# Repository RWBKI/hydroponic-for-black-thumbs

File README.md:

# Hydroponic for Black Thumbs

> I couldn't even grow parsley. So I asked Claude for help… and things got a little out of hand.

A home-built, 24-site hydroponic tower, the growing method that keeps it alive, a dashboard that tells you what to do today, a Claude plugin that sets that dashboard up for your own tower, and the (still untested) electronics and firmware meant to automate it. Everything here was worked out in conversation with Claude by someone who started with zero hydroponics knowledge.

This is an independent community project. It is not affiliated with or endorsed by Anthropic.

<p align="center"><em>The dashboard: type your readings, it tells you what to do today. Runs on demo data until you press "Start fresh".</em><br><strong><a href="https://rwbki.github.io/hydroponic-for-black-thumbs/dashboard/">▶ Try it live in your browser</a></strong><br><em><a href="dashboard/">Download it</a> or let the <a href="plugins/hydroponic-for-black-thumbs/">Claude plugin</a> set it up for your tower.</em></p>

<h3 align="center">The results</h3>

<p align="center"><em>Two neighbouring parsley plants, one stem cut from each. Soil on the left, tower on the right.</em></p>

## What works and what doesn't (yet)

Read this table before you copy anything.

| Part | Status |
|---|---|
| The tower: 24 sites, one shared reservoir, leafy greens and herbs | Running since September 2026 |
| [Growing guide](docs/growing-guide.md): doses, mixing order, routine, troubleshooting | In daily use on the real tower |
| [Dashboard](dashboard/): enter pH / EC / level, get today's actions | Rewritten in English from the one in daily use on the real tower |
| [Claude plugin](plugins/hydroponic-for-black-thumbs/): sets up the dashboard for your tower and coaches you | Works in the Claude app |
| [Automation plan](docs/automation-plan.md): sensors, dosing rules, safeguards | Designed, not built |
| [Wiring guide](docs/wiring.md): module-based controller, pin by pin | Designed, parts ordered, not assembled |
| [Custom PCB v1.1](docs/pcb.md) | Designed, [reviewed](hardware/pcb/docs/REVIEW-rev1.0.md), revised and [reviewed again](hardware/pcb/docs/REVIEW-rev1.1.md): **never fabricated, untested** |
| [Firmware](firmware/) for the ESP32: readings, web page, dosing with safeguards | Written, compiles, dosing logic covered by automated tests. **Never run on hardware** |

Building the tower itself is not covered: there are plenty of tutorials for that. This repository covers what comes after.

If you are an electronics engineer, the most useful thing you can do is review the schematic. See [CONTRIBUTING.md](CONTRIBUTING.md).

## The tower in numbers

| | |
|---|---|
| Sites | 24, in 4 columns of 6 |
| Reservoir | 37 L (started at 15 L, which drifted too fast) |
| Medium | Expanded clay pebbles, with a coco or rockwool plug at the collar |
| Nutrients | Terra Aquatica TriPart (Micro, Grow, Bloom) |
| Targets | EC 1.0 to 1.2 mS/cm, pH 6.0 (5.5 to 6.5 acceptable) |
| Light | Natural light only, under an open-sided shelter |
| Crops | Lettuce, basil, chives, parsley, lamb's lettuce, spinach |
| Routine | 3 minutes every 2 to 3 days; full drain every 15 to 21 days |

## Where to start

**I want to grow things.** Read the [growing guide](docs/growing-guide.md). You need a pH meter, an EC meter and pH Down. Nothing in it requires electronics.

**I want to try the dashboard.** Download [`dashboard/index.html`](dashboard/index.html) and open it in a browser. It starts with demo data, needs no server or account, and keeps your data in that browser.

**I want it in my own Claude.** Install the plugin (below). Claude asks a few questions about your tower, water and nutrients, creates your dashboard, and then advises you from your own readings.

**I want to automate.** Read the [automation plan](docs/automation-plan.md) first, safeguards included, then the [wiring guide](docs/wiring.md) and the [firmware](firmware/). The [PCB](docs/pcb.md) is optional and unproven.

**I want to know what it costs.** See [costs](docs/costs.md). Short version: the automation parts come to roughly €200.

## Use it with Claude

The plugin contains one skill, `hydroponic-tower-coach`.

**Claude apps, as a plugin** (paid plans): Customize → Plugins → Personal plugins → "+" → Add marketplace → Add from a repository, then paste this repository's URL and install `hydroponic-for-black-thumbs`.

**Claude apps, as a skill only** (all plans): download `hydroponic-tower-coach.zip` from the Releases page, then Customize → Skills → "+" → Create skill → Upload a skill.

**Claude Code:**

```
/plugin marketplace add RWBKI/hydroponic-for-black-thumbs
/plugin install hydroponic-for-black-thumbs@hydroponic-for-black-thumbs
```

Then say: "Set up my hydroponic tower dashboard."

Later, press "Copy summary for Claude" on the dashboard, paste it into a conversation and ask your question.

Menu names may change; see Anthropic's help pages on [skills](https://support.claude.com/en/articles/12512180-use-skills-in-claude) and [plugins](https://support.claude.com/en/articles/13851150-install-financial-services-plugins).

## Safety

- Water and electricity share a box in this project. No mains voltage goes inside the controller enclosure: the 12 V power brick stays dry, on an outdoor socket protected by an RCD/GFCI.
- pH Down is acid. Add it in small doses to the full volume of water, never to other concentrates.
- Automated dosing can kill a reservoir faster than neglect. The [safeguards](docs/automation-plan.md#safeguards-before-autonomy) are not optional.
- The doses in this repo were calibrated on one water supply and one EC pen. Measure yours.

## Licence

- Code (dashboard, firmware, plugin): [MIT](LICENSE)
- Hardware (schematic, PCB): [CERN-OHL-P v2](hardware/LICENSE)
- Documentation and photos: [CC BY 4.0](docs/LICENSE)

Copyright © 2026 RWBKI and contributors. To credit the project: "Hydroponic for Black Thumbs, by RWBKI and contributors", with a link to this repository.

## Origin

The project was first shared on r/ClaudeAI in November 2026. The questions asked there shaped this repository.

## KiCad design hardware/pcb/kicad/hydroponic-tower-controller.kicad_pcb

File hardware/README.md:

# Hardware

| Folder | Contents |
|---|---|
| `pcb/kicad/` | KiCad 7 project: schematic, routed board, two project footprints |
| `pcb/fabrication/` | Gerbers and drill files (zip), BOM and placement file for JLCPCB assembly |
| `pcb/docs/` | Schematic and assembly drawing as PDF, the two design reviews |
| `pcb/images/` | Layout and silkscreen views |
| `pcb/tools/` | Scripts that re-check the isolation gap, the guard ring and schematic against board |
| `pcb/CHANGES.md` | What changed in rev 1.1 |

**The board has never been fabricated.** Read [docs/pcb.md](../docs/pcb.md) before using anything here.

Hardware in this folder is released under [CERN-OHL-P v2](LICENSE).

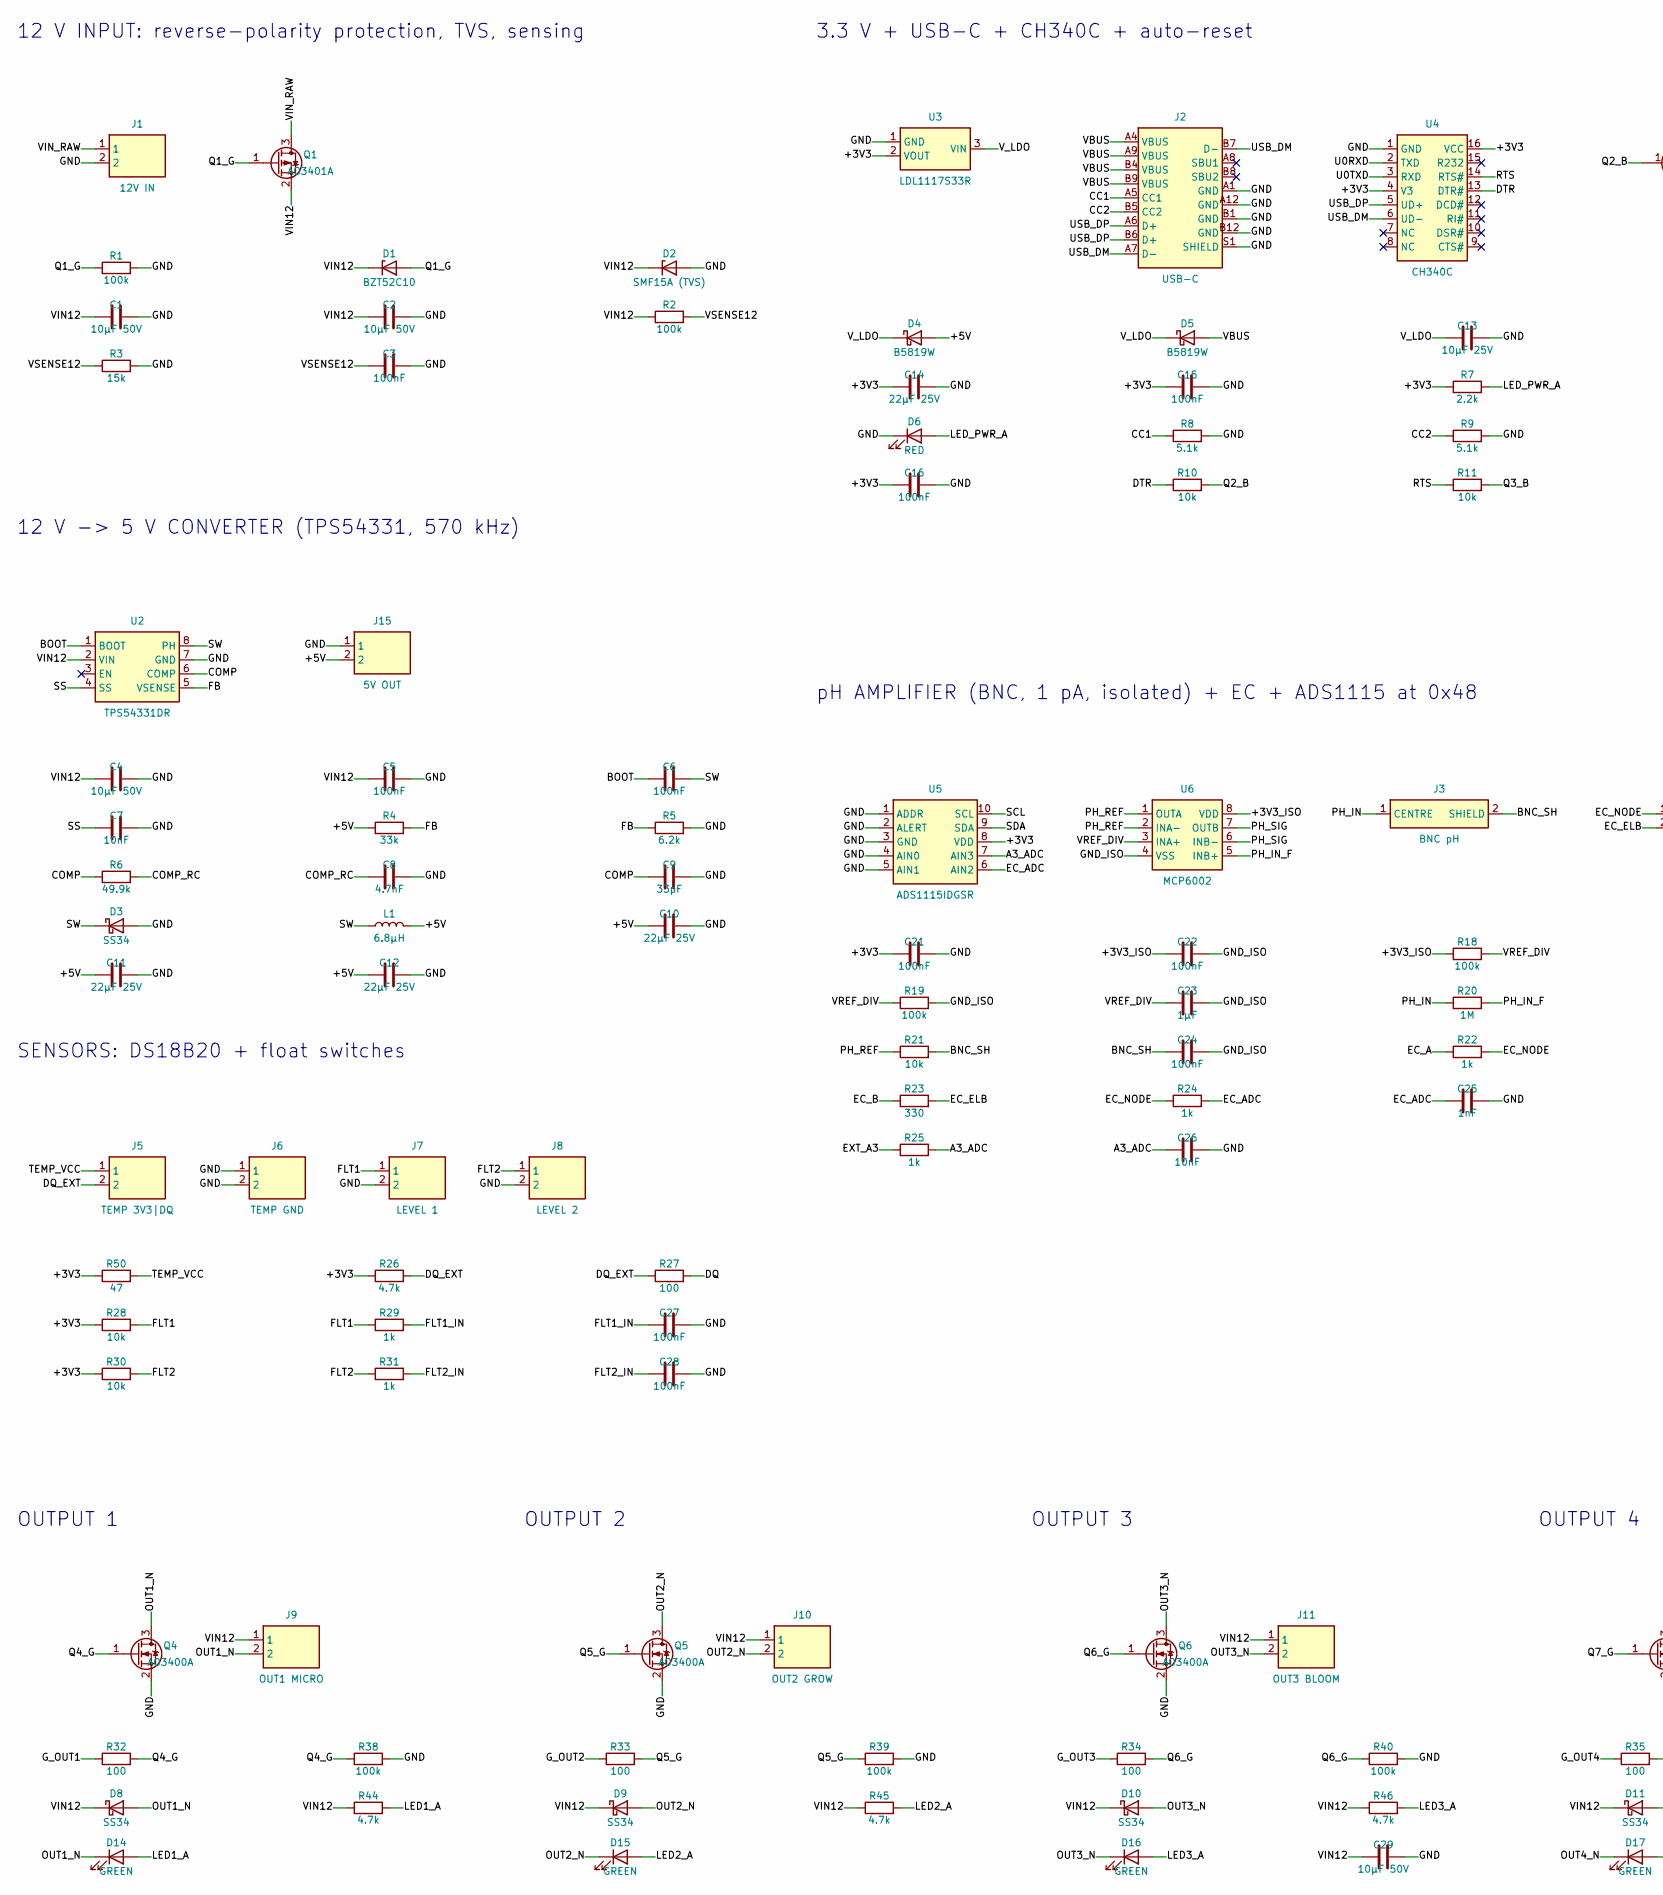
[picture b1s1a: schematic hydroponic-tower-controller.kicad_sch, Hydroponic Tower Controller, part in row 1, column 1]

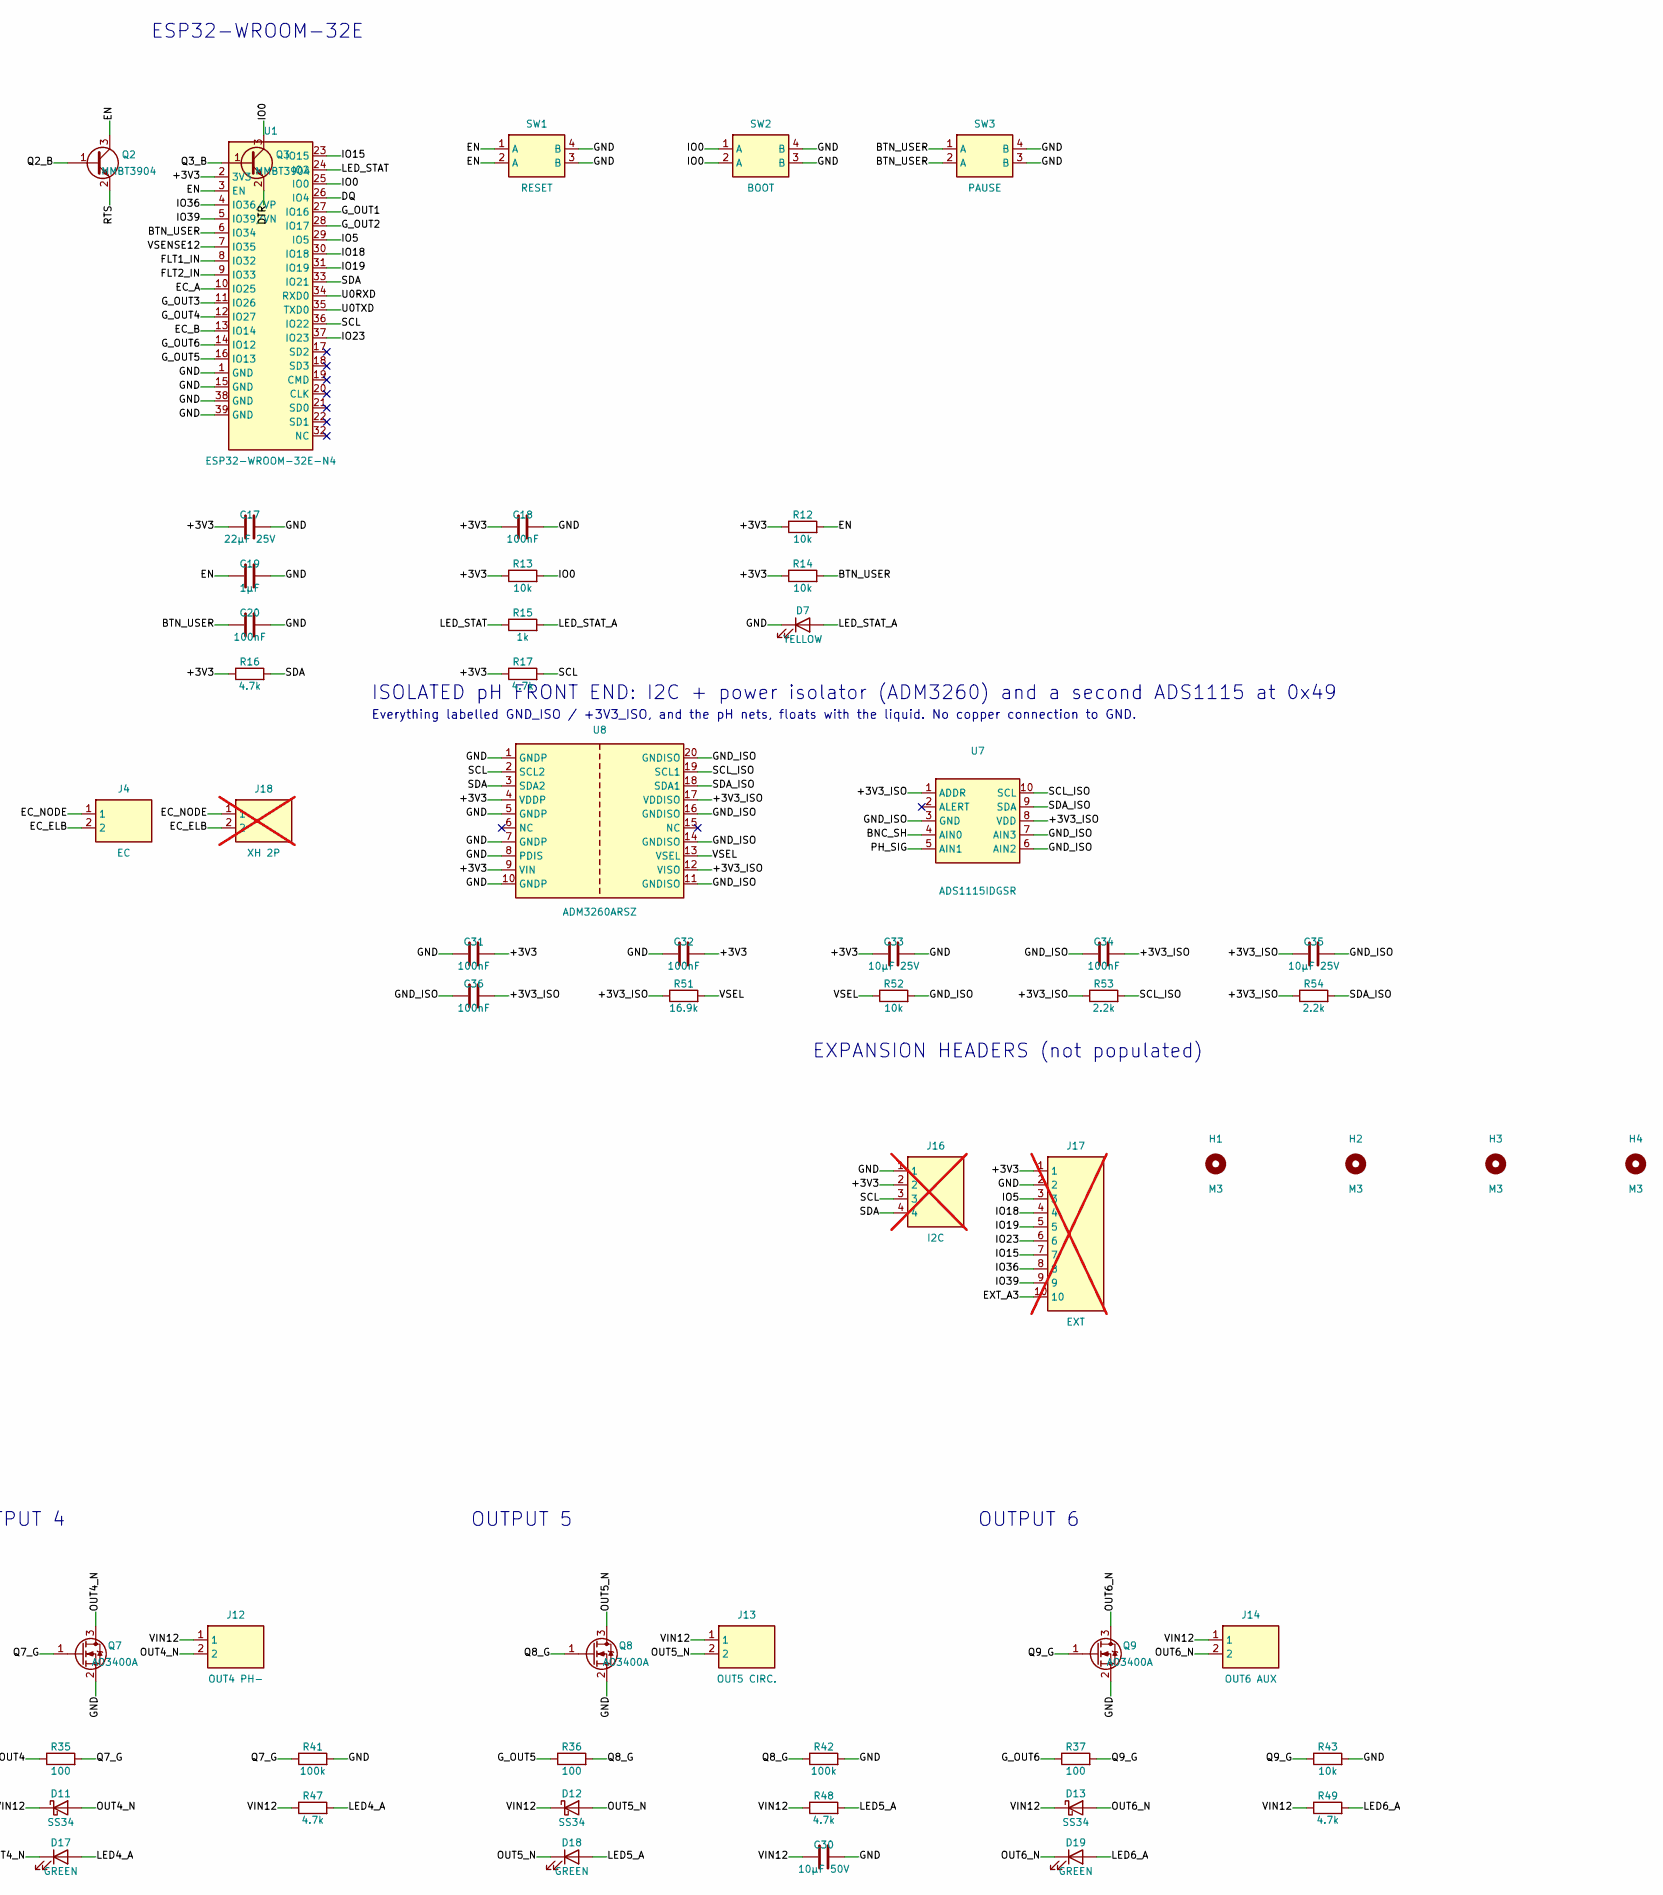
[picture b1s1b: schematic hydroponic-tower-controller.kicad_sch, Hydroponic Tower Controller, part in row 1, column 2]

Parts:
C1, C2, C4, C29, C30: 10µF 50V; C_1206_3216Metric; LCSC C13585
C3, C5, C6, C15, C16, C18, C20, C21, C22, C24, C27, C28, C31, C32, C36: 100nF; C_0603_1608Metric; LCSC C14663
C7, C26: 10nF; C_0603_1608Metric; LCSC C57112
C8: 4.7nF; C_0603_1608Metric; LCSC C53987
C9: 33pF; C_0603_1608Metric; LCSC C1663
C10, C11, C12: 22µF 25V; C_1206_3216Metric; LCSC C12891
C13, C33, C35: 10µF 25V; C_0805_2012Metric; LCSC C15850
C14, C17: 22µF 25V; C_0805_2012Metric; LCSC C45783
C19, C23: 1µF; C_0603_1608Metric; LCSC C15849
C25: 1nF; C_0603_1608Metric; LCSC C1588
C34: 100nF; C_0402_1005Metric; LCSC C1525
D1: BZT52C10; D_SOD-123; LCSC C19077408
D2: SMF15A (TVS); D_SOD-123F; LCSC C19077509
D3, D8, D9, D10, D11, D12, D13: SS34; D_SMA; LCSC C8678
D4, D5: B5819W; D_SOD-123; LCSC C8598
D6: RED; LED_0603_1608Metric; LCSC C2286
D7: YELLOW; LED_0805_2012Metric; LCSC C2296
D14, D15, D16, D17, D18, D19: GREEN; LED_0805_2012Metric; LCSC C2297
H1, H2, H3, H4: M3; MountingHole_3.2mm_M3
J1: 12V IN; TerminalBlock_Phoenix_MKDS-1,5-2_1x02_P5.00mm_Horizontal; LCSC C474881
J2: USB-C; USB_C_Receptacle_HRO_TYPE-C-31-M-12; LCSC C165948
J3: BNC pH; BNC_Amphenol_B6252HB-NPP3G-50_Horizontal; LCSC C22457552
J4: EC; TerminalBlock_Phoenix_MKDS-1,5-2_1x02_P5.00mm_Horizontal; LCSC C474881
J5: TEMP 3V3|DQ; TerminalBlock_Phoenix_MKDS-1,5-2_1x02_P5.00mm_Horizontal; LCSC C474881
J6: TEMP GND; TerminalBlock_Phoenix_MKDS-1,5-2_1x02_P5.00mm_Horizontal; LCSC C474881
J7: LEVEL 1; TerminalBlock_Phoenix_MKDS-1,5-2_1x02_P5.00mm_Horizontal; LCSC C474881
J8: LEVEL 2; TerminalBlock_Phoenix_MKDS-1,5-2_1x02_P5.00mm_Horizontal; LCSC C474881
J9: OUT1 MICRO; TerminalBlock_Phoenix_MKDS-1,5-2_1x02_P5.00mm_Horizontal; LCSC C474881
J10: OUT2 GROW; TerminalBlock_Phoenix_MKDS-1,5-2_1x02_P5.00mm_Horizontal; LCSC C474881
J11: OUT3 BLOOM; TerminalBlock_Phoenix_MKDS-1,5-2_1x02_P5.00mm_Horizontal; LCSC C474881
J12: OUT4 PH-; TerminalBlock_Phoenix_MKDS-1,5-2_1x02_P5.00mm_Horizontal; LCSC C474881
J13: OUT5 CIRC.; TerminalBlock_Phoenix_MKDS-1,5-2_1x02_P5.00mm_Horizontal; LCSC C474881
J14: OUT6 AUX; TerminalBlock_Phoenix_MKDS-1,5-2_1x02_P5.00mm_Horizontal; LCSC C474881
J15: 5V OUT; TerminalBlock_Phoenix_MKDS-1,5-2_1x02_P5.00mm_Horizontal; LCSC C474881
J16: I2C; PinHeader_1x04_P2.54mm_Vertical; not fitted
J17: EXT; PinHeader_1x10_P2.54mm_Vertical; not fitted
J18: XH 2P; JST_XH_B2B-XH-A_1x02_P2.50mm_Vertical; not fitted
L1: 6.8µH; L_Cenker_CKCS6045; LCSC C354631
Q1: AO3401A; SOT-23; LCSC C15127
Q2, Q3: MMBT3904; SOT-23; LCSC C20526
Q4, Q5, Q6, Q7, Q8, Q9: AO3400A; SOT-23; LCSC C20917
R1, R2, R18, R19, R38, R39, R40, R41, R42: 100k; R_0603_1608Metric; LCSC C25803
R3: 15k; R_0603_1608Metric; LCSC C22809
R4: 33k; R_0603_1608Metric; LCSC C4216
R5: 6.2k; R_0603_1608Metric; LCSC C4260
R6: 49.9k; R_0603_1608Metric; LCSC C23184
R7, R53, R54: 2.2k; R_0603_1608Metric; LCSC C4190
R8, R9: 5.1k; R_0603_1608Metric; LCSC C23186
R10, R11, R12, R13, R14, R21, R28, R30, R43, R52: 10k; R_0603_1608Metric; LCSC C25804
R15, R22, R24, R25, R29, R31: 1k; R_0603_1608Metric; LCSC C21190
R16, R17, R26, R44, R45, R46, R47, R48, R49: 4.7k; R_0603_1608Metric; LCSC C23162
R20: 1M; R_0603_1608Metric; LCSC C22935
R23: 330; R_0603_1608Metric; LCSC C23138
R27, R32, R33, R34, R35, R36, R37: 100; R_0603_1608Metric; LCSC C22775
R50: 47; R_0603_1608Metric; LCSC C23182
R51: 16.9k; R_0603_1608Metric; LCSC C25954
SW1: RESET; SW_TS-1187A_5.1x5.1mm; LCSC C318884
SW2: BOOT; SW_TS-1187A_5.1x5.1mm; LCSC C318884
SW3: PAUSE; SW_TS-1187A_5.1x5.1mm; LCSC C318884
U1: ESP32-WROOM-32E-N4; ESP32-WROOM-32E; LCSC C701341
U2: TPS54331DR; SOIC-8_3.9x4.9mm_P1.27mm; LCSC C9865
U3: LDL1117S33R; SOT-223-3_TabPin2; LCSC C435835
U4: CH340C; SOIC-16_3.9x9.9mm_P1.27mm; LCSC C84681
U5, U7: ADS1115IDGSR; VSSOP-10_3x3mm_P0.5mm; LCSC C37593
U6: MCP6002; SOIC-8_3.9x4.9mm_P1.27mm; LCSC C7377
U8: ADM3260ARSZ; SSOP-20_5.3x7.2mm_P0.65mm; LCSC C208558

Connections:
+3V3: C14.1, C15.1, C16.1, C17.1, C18.1, C21.1, C31.2, C32.2, C33.1, J16.2, J17.1, R7.1, R12.1, R13.1, R14.1, R16.1, R17.1, R26.1, R28.1, R30.1, R50.1, U1.2 (3V3), U3.2 (VOUT), U4.4 (V3), U4.16 (VCC), U5.8 (VDD), U8.4 (VDDP), U8.9 (VIN)
+3V3_ISO: C22.1, C34.2, C35.1, C36.2, R18.1, R51.1, R53.1, R54.1, U6.8 (VDD), U7.1 (ADDR), U7.8 (VDD), U8.12 (VISO), U8.17 (VDDISO)
+5V: C10.1, C11.1, C12.1, D4.2 (A), J15.2, L1.2, R4.1
A3_ADC: C26.1, R25.2, U5.7 (AIN3)
BNC_SH: C24.1, J3.2 (SHIELD), R21.2, U7.4 (AIN0)
BOOT: C6.1, U2.1 (BOOT)
BTN_USER: C20.1, R14.2, SW3.1 (A), SW3.2 (A), U1.6 (IO34)
CC1: J2.A5 (CC1), R8.1
CC2: J2.B5 (CC2), R9.1
COMP: C9.1, R6.1, U2.6 (COMP)
COMP_RC: C8.1, R6.2
DQ: R27.2, U1.26 (IO4)
DQ_EXT: J5.2, R26.2, R27.1
DTR: Q3.2 (E), R10.1, U4.13 (DTR#)
EC_A: R22.1, U1.10 (IO25)
EC_ADC: C25.1, R24.2, U5.6 (AIN2)
EC_B: R23.1, U1.13 (IO14)
EC_ELB: J4.2, J18.2, R23.2
EC_NODE: J4.1, J18.1, R22.2, R24.1
EN: C19.1, Q2.3 (C), R12.2, SW1.1 (A), SW1.2 (A), U1.3 (EN)
EXT_A3: J17.10, R25.1
FB: R4.2, R5.1, U2.5 (VSENSE)
FLT1: J7.1, R28.2, R29.1
FLT1_IN: C27.1, R29.2, U1.8 (IO32)
FLT2: J8.1, R30.2, R31.1
FLT2_IN: C28.1, R31.2, U1.9 (IO33)
GND: C1.2, C2.2, C3.2, C4.2, C5.2, C7.2, C8.2, C9.2, C10.2, C11.2, C12.2, C13.2, C14.2, C15.2, C16.2, C17.2, C18.2, C19.2, C20.2, C21.2, C25.2, C26.2, C27.2, C28.2, C29.2, C30.2, C31.1, C32.1, C33.2, D2.2 (A), D3.2 (A), D6.1 (K), D7.1 (K), J1.2, J2.A1 (GND), J2.A12 (GND), J2.B1 (GND), J2.B12 (GND), J2.S1 (SHIELD), J6.1, J6.2, J7.2, J8.2, J15.1, J16.1, J17.2, Q4.2 (S), Q5.2 (S), Q6.2 (S), Q7.2 (S), Q8.2 (S), Q9.2 (S), R1.2, R3.2, R5.2, R8.2, R9.2, R38.2, R39.2, R40.2, R41.2, R42.2, R43.2, SW1.3 (B), SW1.4 (B), SW2.3 (B), SW2.4 (B), SW3.3 (B), SW3.4 (B), U1.1 (GND), U1.15 (GND), U1.38 (GND), U1.39 (GND), U2.7 (GND), U3.1 (GND), U4.1 (GND), U5.1 (ADDR), U5.2 (ALERT), U5.3 (GND), U5.4 (AIN0), U5.5 (AIN1), U8.1 (GNDP), U8.5 (GNDP), U8.7 (GNDP), U8.8 (PDIS), U8.10 (GNDP)
GND_ISO: C22.2, C23.2, C24.2, C34.1, C35.2, C36.1, R19.2, R52.2, U6.4 (VSS), U7.3 (GND), U7.6 (AIN2), U7.7 (AIN3), U8.11 (GNDISO), U8.14 (GNDISO), U8.16 (GNDISO), U8.20 (GNDISO)
G_OUT1: R32.1, U1.27 (IO16)
G_OUT2: R33.1, U1.28 (IO17)
G_OUT3: R34.1, U1.11 (IO26)
G_OUT4: R35.1, U1.12 (IO27)
G_OUT5: R36.1, U1.16 (IO13)
G_OUT6: R37.1, U1.14 (IO12)
IO0: Q3.3 (C), R13.2, SW2.1 (A), SW2.2 (A), U1.25 (IO0)
IO5: J17.3, U1.29 (IO5)
IO15: J17.7, U1.23 (IO15)
IO18: J17.4, U1.30 (IO18)
IO19: J17.5, U1.31 (IO19)
IO23: J17.6, U1.37 (IO23)
IO36: J17.8, U1.4 (IO36/VP)
IO39: J17.9, U1.5 (IO39/VN)
LED1_A: D14.2 (A), R44.2
LED2_A: D15.2 (A), R45.2
LED3_A: D16.2 (A), R46.2
LED4_A: D17.2 (A), R47.2
LED5_A: D18.2 (A), R48.2
LED6_A: D19.2 (A), R49.2
LED_PWR_A: D6.2 (A), R7.2
LED_STAT: R15.1, U1.24 (IO2)
LED_STAT_A: D7.2 (A), R15.2
OUT1_N: D8.2 (A), D14.1 (K), J9.2, Q4.3 (D)
OUT2_N: D9.2 (A), D15.1 (K), J10.2, Q5.3 (D)
OUT3_N: D10.2 (A), D16.1 (K), J11.2, Q6.3 (D)
OUT4_N: D11.2 (A), D17.1 (K), J12.2, Q7.3 (D)
OUT5_N: D12.2 (A), D18.1 (K), J13.2, Q8.3 (D)
OUT6_N: D13.2 (A), D19.1 (K), J14.2, Q9.3 (D)
PH_IN: J3.1 (CENTRE), R20.1
PH_IN_F: R20.2, U6.5 (INB+)
PH_REF: R21.1, U6.1 (OUTA), U6.2 (INA-)
PH_SIG: U6.6 (INB-), U6.7 (OUTB), U7.5 (AIN1)
Q1_G: D1.2 (A), Q1.1 (G), R1.1
Q2_B: Q2.1 (B), R10.2
Q3_B: Q3.1 (B), R11.2
Q4_G: Q4.1 (G), R32.2, R38.1
Q5_G: Q5.1 (G), R33.2, R39.1
Q6_G: Q6.1 (G), R34.2, R40.1
Q7_G: Q7.1 (G), R35.2, R41.1
Q8_G: Q8.1 (G), R36.2, R42.1
Q9_G: Q9.1 (G), R37.2, R43.1
RTS: Q2.2 (E), R11.1, U4.14 (RTS#)
SCL: J16.3, R17.2, U1.36 (IO22), U5.10 (SCL), U8.2 (SCL2)
SCL_ISO: R53.2, U7.10 (SCL), U8.19 (SCL1)
SDA: J16.4, R16.2, U1.33 (IO21), U5.9 (SDA), U8.3 (SDA2)
SDA_ISO: R54.2, U7.9 (SDA), U8.18 (SDA1)
SS: C7.1, U2.4 (SS)
SW: C6.2, D3.1 (K), L1.1, U2.8 (PH)
TEMP_VCC: J5.1, R50.2
U0RXD: U1.34 (RXD0), U4.2 (TXD)
U0TXD: U1.35 (TXD0), U4.3 (RXD)
USB_DM: J2.A7 (D-), J2.B7 (D-), U4.6 (UD-)
USB_DP: J2.A6 (D+), J2.B6 (D+), U4.5 (UD+)
VBUS: D5.2 (A), J2.A4 (VBUS), J2.A9 (VBUS), J2.B4 (VBUS), J2.B9 (VBUS)
VIN12: C1.1, C2.1, C4.1, C5.1, C29.1, C30.1, D1.1 (K), D2.1 (K), D8.1 (K), D9.1 (K), D10.1 (K), D11.1 (K), D12.1 (K), D13.1 (K), J9.1, J10.1, J11.1, J12.1, J13.1, J14.1, Q1.2 (S), R2.1, R44.1, R45.1, R46.1, R47.1, R48.1, R49.1, U2.2 (VIN)
VIN_RAW: J1.1, Q1.3 (D)
VREF_DIV: C23.1, R18.2, R19.1, U6.3 (INA+)
VSEL: R51.2, R52.1, U8.13 (VSEL)
VSENSE12: C3.1, R2.2, R3.1, U1.7 (IO35)
V_LDO: C13.1, D4.1 (K), D5.1 (K), U3.3 (VIN)

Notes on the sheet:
12 V INPUT: reverse-polarity protection, TVS, sensing
12 V -> 5 V CONVERTER (TPS54331, 570 kHz)
3.3 V + USB-C + CH340C + auto-reset
ESP32-WROOM-32E
pH AMPLIFIER (BNC, 1 pA, isolated) + EC + ADS1115 at 0x48
SENSORS: DS18B20 + float switches
EXPANSION HEADERS (not populated)
OUTPUT 1
OUTPUT 2
OUTPUT 3
OUTPUT 4
OUTPUT 5
OUTPUT 6
ISOLATED pH FRONT END: I2C + power isolator (ADM3260) and a second ADS1115 at 0x49
Everything labelled GND_ISO / +3V3_ISO, and the pH nets, floats with the liquid. No copper connection to GND.

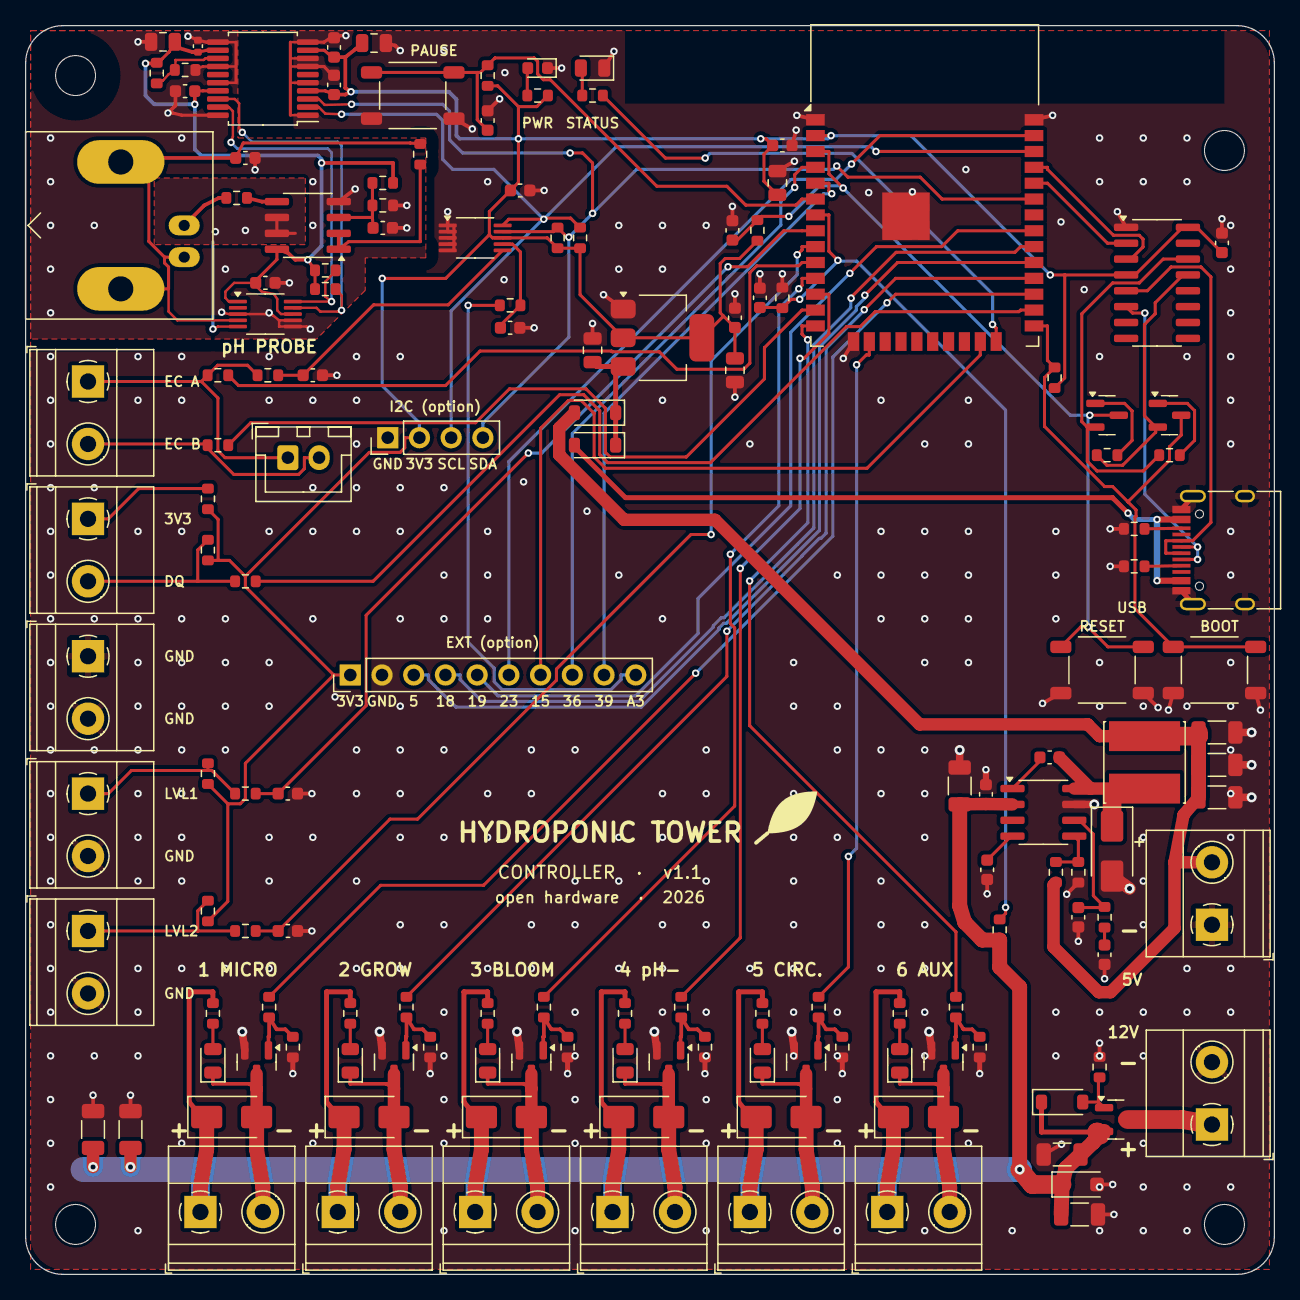
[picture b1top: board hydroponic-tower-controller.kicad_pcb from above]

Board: 2 copper layers, 100.0 x 100.0 mm, 152 parts (0 on the bottom side), 89 nets.

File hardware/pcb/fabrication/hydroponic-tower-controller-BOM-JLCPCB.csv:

Comment,Designator,Footprint,LCSC Part #
KF301-5.0-2P,"J1,J4,J5,J6,J7,J8,J9,J10,J11,J12,J13,J14,J15","TerminalBlock_Phoenix_MKDS-1,5-2_1x02_P5.00mm_Horizontal",C474881
AO3401A,Q1,SOT-23,C15127
100k,"R1,R2,R18,R19,R38,R39,R40,R41,R42",R_0603_1608Metric,C25803
BZT52C10,D1,D_SOD-123,C19077408
SMF15A,D2,D_SOD-123F,C19077509
10µF 50V,"C1,C2,C4,C29,C30",C_1206_3216Metric,C13585
15k,R3,R_0603_1608Metric,C22809
100nF,"C3,C5,C6,C15,C16,C18,C20,C21,C22,C24,C27,C28,C31,C32,C36",C_0603_1608Metric,C14663
TPS54331DR,U2,SOIC-8_3.9x4.9mm_P1.27mm,C9865
10nF,"C7,C26",C_0603_1608Metric,C57112
33k,R4,R_0603_1608Metric,C4216
6.2k,R5,R_0603_1608Metric,C4260
49.9k,R6,R_0603_1608Metric,C23184
4.7nF,C8,C_0603_1608Metric,C53987
33pF,C9,C_0603_1608Metric,C1663
SS34,"D3,D8,D9,D10,D11,D12,D13",D_SMA,C8678
6.8µH,L1,L_Cenker_CKCS6045,C354631
22µF 25V,"C10,C11,C12",C_1206_3216Metric,C12891
B5819W,"D4,D5",D_SOD-123,C8598
LDL1117S33R,U3,SOT-223-3_TabPin2,C435835
10µF 25V,"C13,C33,C35",C_0805_2012Metric,C15850
22µF 25V,"C14,C17",C_0805_2012Metric,C45783
2.2k,"R7,R53,R54",R_0603_1608Metric,C4190
RED,D6,LED_0603_1608Metric,C2286
USB-C,J2,USB_C_Receptacle_HRO_TYPE-C-31-M-12,C165948
5.1k,"R8,R9",R_0603_1608Metric,C23186
CH340C,U4,SOIC-16_3.9x9.9mm_P1.27mm,C84681
MMBT3904,"Q2,Q3",SOT-23,C20526
10k,"R10,R11,R12,R13,R14,R21,R28,R30,R43,R52",R_0603_1608Metric,C25804
ESP32-WROOM-32E-N4,U1,ESP32-WROOM-32E,C701341
1µF,"C19,C23",C_0603_1608Metric,C15849
TS-1187A-B-A-B,"SW1,SW2,SW3",SW_TS-1187A_5.1x5.1mm,C318884
1k,"R15,R22,R24,R25,R29,R31",R_0603_1608Metric,C21190
YELLOW,D7,LED_0805_2012Metric,C2296
4.7k,"R16,R17,R26,R44,R45,R46,R47,R48,R49",R_0603_1608Metric,C23162
ADS1115IDGSR,"U5,U7",VSSOP-10_3x3mm_P0.5mm,C37593
MCP6002,U6,SOIC-8_3.9x4.9mm_P1.27mm,C7377
BNC pH,J3,BNC_Amphenol_B6252HB-NPP3G-50_Horizontal,C22457552
1M,R20,R_0603_1608Metric,C22935
330,R23,R_0603_1608Metric,C23138
1nF,C25,C_0603_1608Metric,C1588
47,R50,R_0603_1608Metric,C23182
100,"R27,R32,R33,R34,R35,R36,R37",R_0603_1608Metric,C22775
AO3400A,"Q4,Q5,Q6,Q7,Q8,Q9",SOT-23,C20917
GREEN,"D14,D15,D16,D17,D18,D19",LED_0805_2012Metric,C2297
100nF,C34,C_0402_1005Metric,C1525
16.9k,R51,R_0603_1608Metric,C25954
ADM3260ARSZ,U8,SSOP-20_5.3x7.2mm_P0.65mm,C208558

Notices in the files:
hardware/pcb/kicad/hydroponic-tower-controller.kicad_sch:
Open hardware - CERN-OHL-P v2
